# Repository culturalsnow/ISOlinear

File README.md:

ISOlinear is an ortholinear keyboard with the ISO Enter key.

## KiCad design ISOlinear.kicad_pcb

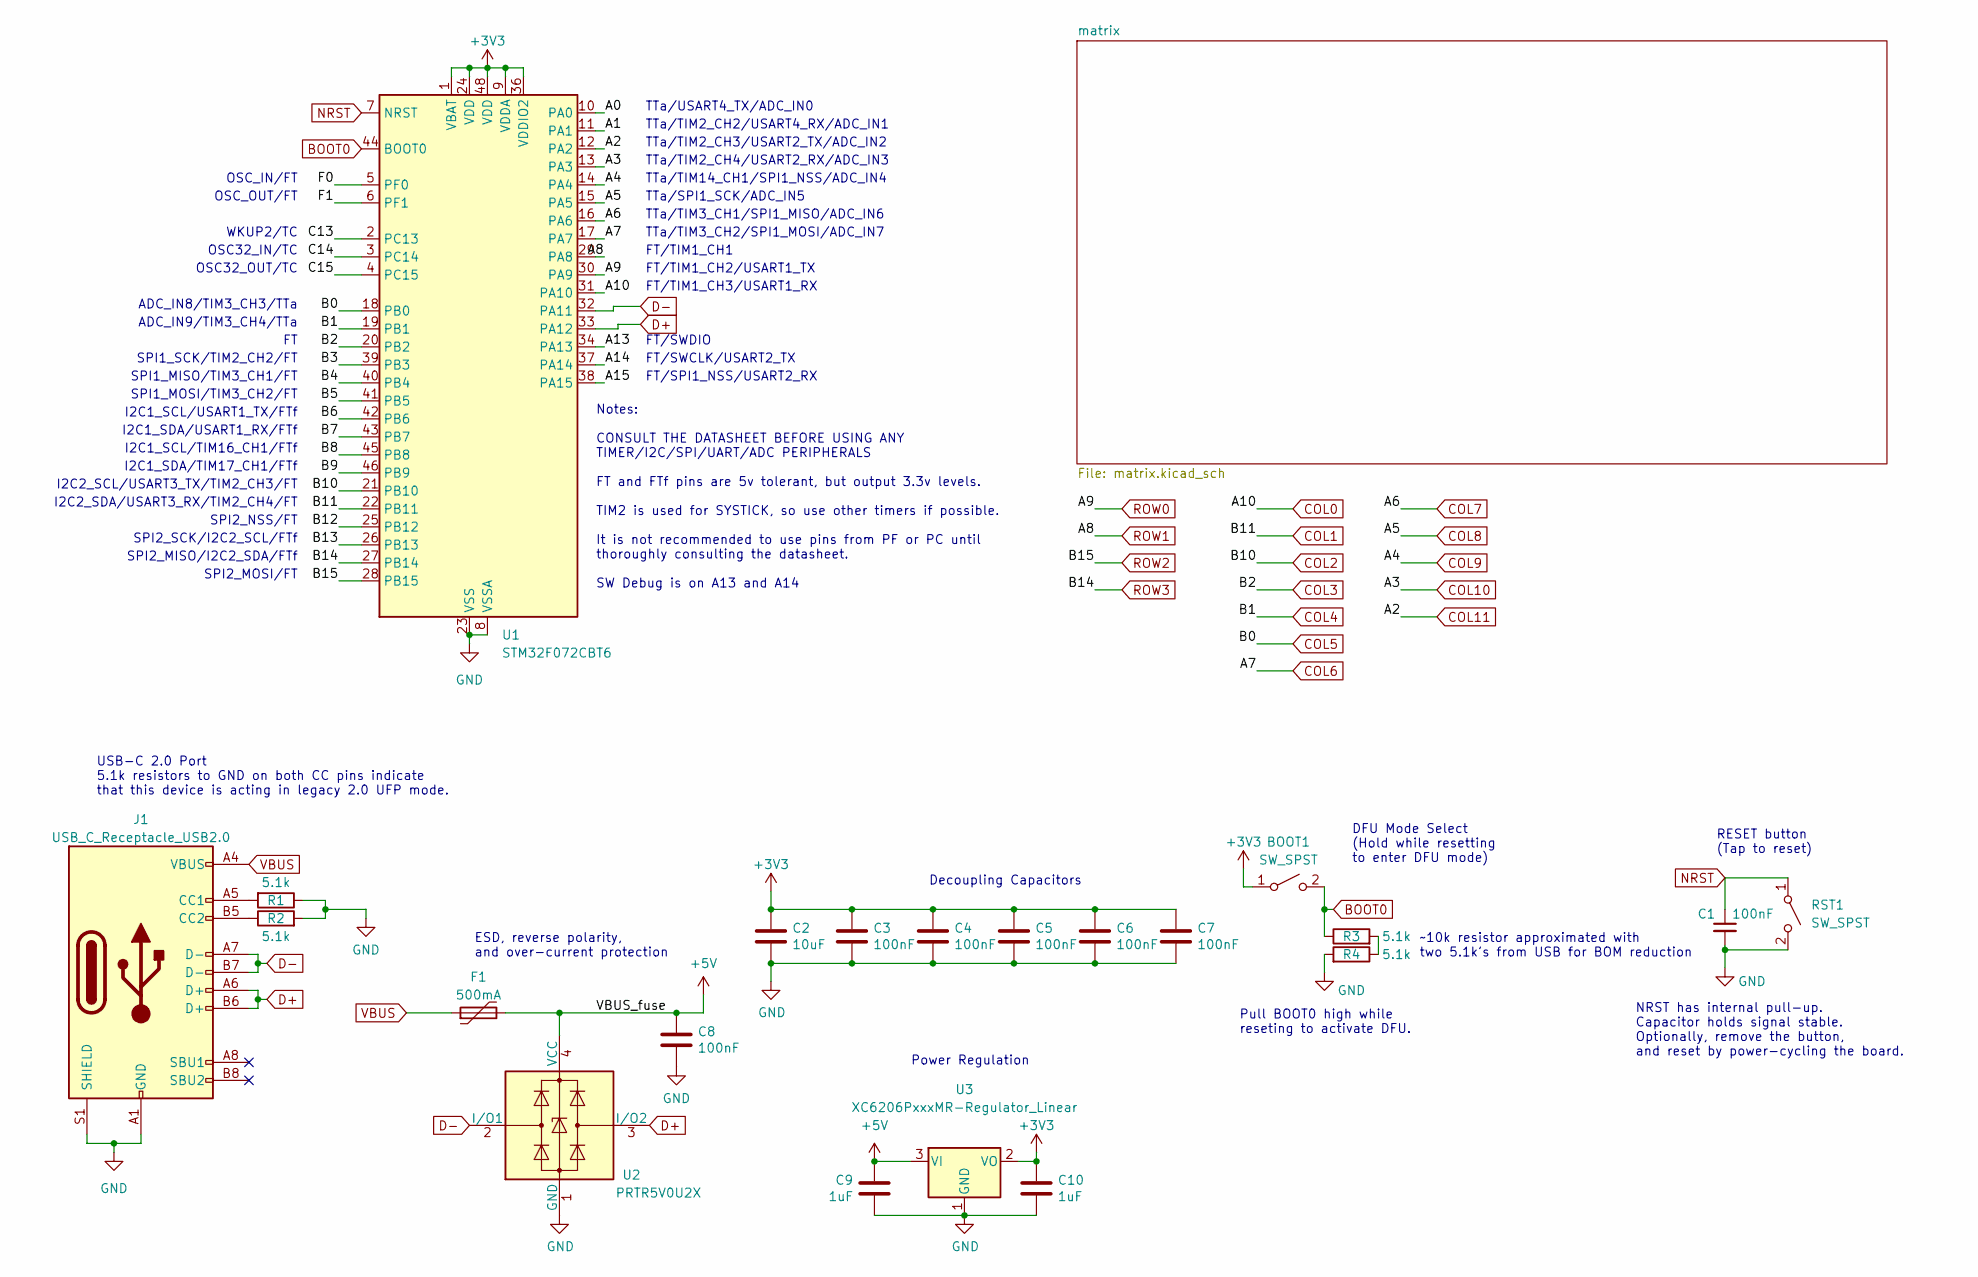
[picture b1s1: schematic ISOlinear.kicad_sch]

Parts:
BOOT1: SW_SPST; SW_SPST_TL3342
C1, C3, C4, C5, C6, C7, C8: 100nF; C_0402_1005Metric; LCSC C307331
C2: 10uF; C_0603_1608Metric; LCSC C307331
C9, C10: 1uF; C_0402_1005Metric; LCSC C307331
F1: 500mA; Fuse_1206_3216Metric; LCSC C135341
J1: USB_C_Receptacle_USB2.0; USB_C_Receptacle_HRO_TYPE-C-31-M-12; JlcRotOffset 180
R1, R2, R3, R4: 5.1k; R_0402_1005Metric
RST1: SW_SPST; SW_SPST_TL3342
U1: STM32F072CBT6; LQFP-48_7x7mm_P0.5mm; JlcRotOffset 90
U2: PRTR5V0U2X; SOT-143; LCSC C2827688
U3: XC6206PxxxMR-Regulator_Linear; SOT-23; LCSC C5446

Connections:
+3V3: BOOT1.1 (A), C2.1, C3.1, C4.1, C5.1, C6.1, C7.1, C10.1, U1.1 (VBAT), U1.9 (VDDA), U1.24 (VDD), U1.36 (VDDIO2), U1.48 (VDD), U3.2 (VO)
+5V: C8.1, C9.1, F1.2, U2.4 (VCC), U3.3 (VI)
/A0: U1.10 (PA0)
/A1: U1.11 (PA1)
/A13: U1.34 (PA13)
/A14: U1.37 (PA14)
/A15: U1.38 (PA15)
/B3: U1.39 (PB3)
/B4: U1.40 (PB4)
/B5: U1.41 (PB5)
/B6: U1.42 (PB6)
/B7: U1.43 (PB7)
/B8: U1.45 (PB8)
/B9: U1.46 (PB9)
/B12: U1.25 (PB12)
/B13: U1.26 (PB13)
/C13: U1.2 (PC13)
/C14: U1.3 (PC14)
/C15: U1.4 (PC15)
/F0: U1.5 (PF0)
/F1: U1.6 (PF1)
BOOT0: BOOT1.2 (B), R3.1, U1.44 (BOOT0)
COL0: U1.31 (PA10); also elsewhere on the board
COL1: U1.22 (PB11); also elsewhere on the board
COL2: U1.21 (PB10); also elsewhere on the board
COL3: U1.20 (PB2); also elsewhere on the board
COL4: U1.19 (PB1); also elsewhere on the board
COL5: U1.18 (PB0); also elsewhere on the board
COL6: U1.17 (PA7); also elsewhere on the board
COL7: U1.16 (PA6); also elsewhere on the board
COL8: U1.15 (PA5); also elsewhere on the board
COL9: U1.14 (PA4); also elsewhere on the board
COL10: U1.13 (PA3); also elsewhere on the board
COL11: U1.12 (PA2); also elsewhere on the board
D+: J1.A6 (D+), J1.B6 (D+), U1.33 (PA12), U2.3 (I/O2)
D-: J1.A7 (D-), J1.B7 (D-), U1.32 (PA11), U2.2 (I/O1)
GND: C1.2, C2.2, C3.2, C4.2, C5.2, C6.2, C7.2, C8.2, C9.2, C10.2, J1.A1 (GND), J1.A12 (GND), J1.B1 (GND), J1.B12 (GND), J1.S1 (SHIELD), R1.1, R2.2, R4.2, RST1.2 (B), U1.8 (VSSA), U1.23 (VSS), U1.35 (VSS), U1.47 (VSS), U2.1 (GND), U3.1 (GND)
NRST: C1.1, RST1.1 (A), U1.7 (NRST)
unnamed: J1.A5 (CC1), R1.2
unnamed: J1.B5 (CC2), R2.1
unnamed: R3.2, R4.1
ROW0: U1.30 (PA9); also elsewhere on the board
ROW1: U1.29 (PA8); also elsewhere on the board
ROW2: U1.28 (PB15); also elsewhere on the board
ROW3: U1.27 (PB14); also elsewhere on the board
VBUS: F1.1, J1.A4 (VBUS), J1.A9 (VBUS), J1.B4 (VBUS), J1.B9 (VBUS)

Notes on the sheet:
SPI1_SCK/TIM2_CH2/FT
FT/TIM1_CH1
FT/TIM1_CH3/USART1_RX
SPI2_NSS/FT
Notes: CONSULT THE DATASHEET BEFORE USING ANY TIMER/I2C/SPI/UART/ADC PERIPHERALS FT and FTf pins are 5v tolerant, but output 3.3v levels. TIM2 is used for SYSTICK, so use other timers if possible. It is not recommended to use pins from PF or PC until thoroughly consulting the datasheet. SW Debug is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
TTa/TIM2_CH4/USART2_RX/ADC_IN3
NRST has internal pull-up. Capacitor holds signal stable. Optionally, remove the button, and reset by power-cycling the board.
FT/SWDIO
Decoupling Capacitors
SPI1_MOSI/TIM3_CH2/FT
ADC_IN9/TIM3_CH4/TTa
I2C2_SCL/USART3_TX/TIM2_CH3/FT
SPI2_MISO/I2C2_SDA/FTf
FT/SWCLK/USART2_TX
I2C1_SCL/TIM16_CH1/FTf
~10k resistor approximated with two 5.1k's from USB for BOM reduction
TTa/TIM2_CH2/USART4_RX/ADC_IN1
USB-C 2.0 Port 5.1k resistors to GND on both CC pins indicate that this device is acting in legacy 2.0 UFP mode.
TTa/TIM2_CH3/USART2_TX/ADC_IN2
OSC_IN/FT
DFU Mode Select (Hold while resetting to enter DFU mode)
WKUP2/TC
I2C2_SDA/USART3_RX/TIM2_CH4/FT
ADC_IN8/TIM3_CH3/TTa
RESET button (Tap to reset)
Pull BOOT0 high while reseting to activate DFU.
I2C1_SDA/TIM17_CH1/FTf
TTa/SPI1_SCK/ADC_IN5
TTa/TIM3_CH1/SPI1_MISO/ADC_IN6
TTa/TIM3_CH2/SPI1_MOSI/ADC_IN7
OSC32_OUT/TC
FT/SPI1_NSS/USART2_RX
SPI1_MISO/TIM3_CH1/FT
OSC32_IN/TC
TTa/TIM14_CH1/SPI1_NSS/ADC_IN4
I2C1_SDA/USART1_RX/FTf
SPI2_MOSI/FT
FT/TIM1_CH2/USART1_TX
Power Regulation
SPI2_SCK/I2C2_SCL/FTf

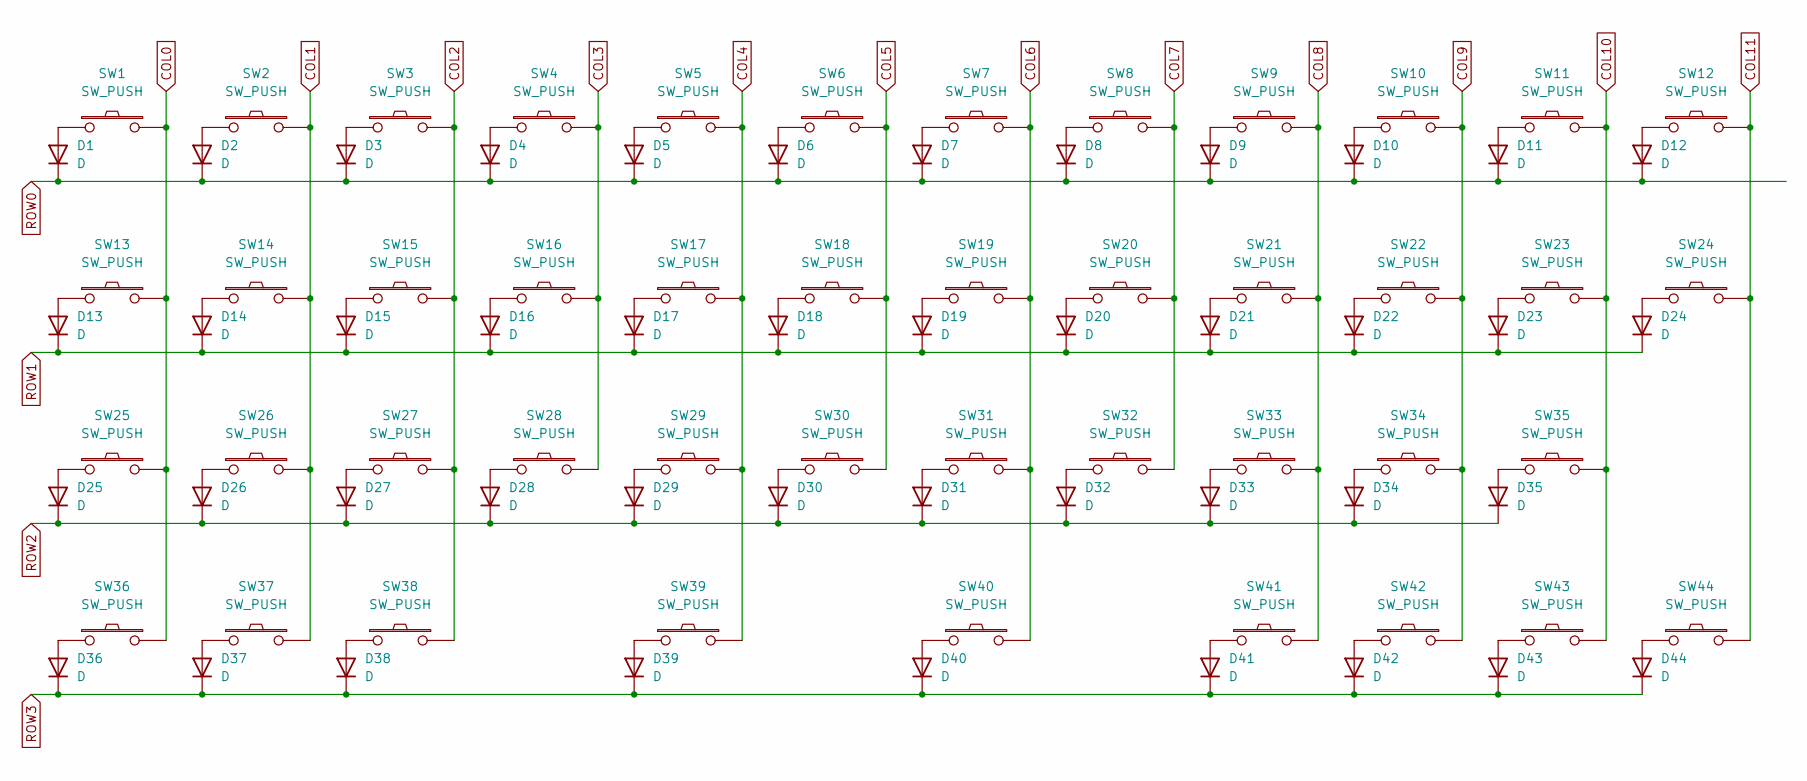
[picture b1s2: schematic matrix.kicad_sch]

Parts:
D1, D2, D3, D4, D5, D6, D7, D8, D9, D10, D11, D12, D13, D14, D15, D16, D17, D18, D19, D20, D21, D22, D23, D24, D25, D26, D27, D28, D29, D30, D31, D32, D33, D34, D35, D36, D37, D38, D39, D40, D41, D42, D43, D44: D; D_SOD-123
SW1, SW2, SW3, SW4, SW5, SW6, SW7, SW8, SW9, SW10, SW11, SW12, SW13, SW14, SW15, SW16, SW17, SW18, SW19, SW20, SW21, SW22, SW23, SW24, SW25, SW26, SW27, SW28, SW29, SW30, SW31, SW32, SW33, SW34, SW35, SW36, SW37, SW38, SW39, SW40, SW41, SW42, SW43, SW44: SW_PUSH; MXOnly-1U-Hotswap

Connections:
COL0: SW1.2, SW13.2, SW25.2, SW36.2; also elsewhere on the board
COL1: SW2.2, SW14.2, SW26.2, SW37.2; also elsewhere on the board
COL2: SW3.2, SW15.2, SW27.2, SW38.2; also elsewhere on the board
COL3: SW4.2, SW16.2, SW28.2; also elsewhere on the board
COL4: SW5.2, SW17.2, SW29.2, SW39.2; also elsewhere on the board
COL5: SW6.2, SW18.2, SW30.2; also elsewhere on the board
COL6: SW7.2, SW19.2, SW31.2, SW40.2; also elsewhere on the board
COL7: SW8.2, SW20.2, SW32.2; also elsewhere on the board
COL8: SW9.2, SW21.2, SW33.2, SW41.2; also elsewhere on the board
COL9: SW10.2, SW22.2, SW34.2, SW42.2; also elsewhere on the board
COL10: SW11.2, SW23.2, SW35.2, SW43.2; also elsewhere on the board
COL11: SW12.2, SW24.2, SW44.2; also elsewhere on the board
unnamed: D1.2 (A), SW1.1
unnamed: D2.2 (A), SW2.1
unnamed: D3.2 (A), SW3.1
unnamed: D4.2 (A), SW4.1
unnamed: D5.2 (A), SW5.1
unnamed: D6.2 (A), SW6.1
unnamed: D7.2 (A), SW7.1
unnamed: D8.2 (A), SW8.1
unnamed: D9.2 (A), SW9.1
unnamed: D10.2 (A), SW10.1
unnamed: D11.2 (A), SW11.1
unnamed: D12.2 (A), SW12.1
unnamed: D13.2 (A), SW13.1
unnamed: D14.2 (A), SW14.1
unnamed: D15.2 (A), SW15.1
unnamed: D16.2 (A), SW16.1
unnamed: D17.2 (A), SW17.1
unnamed: D18.2 (A), SW18.1
unnamed: D19.2 (A), SW19.1
unnamed: D20.2 (A), SW20.1
unnamed: D21.2 (A), SW21.1
unnamed: D22.2 (A), SW22.1
unnamed: D23.2 (A), SW23.1
unnamed: D24.2 (A), SW24.1
unnamed: D25.2 (A), SW25.1
unnamed: D26.2 (A), SW26.1
unnamed: D27.2 (A), SW27.1
unnamed: D28.2 (A), SW28.1
unnamed: D29.2 (A), SW29.1
unnamed: D30.2 (A), SW30.1
unnamed: D31.2 (A), SW31.1
unnamed: D32.2 (A), SW32.1
unnamed: D33.2 (A), SW33.1
unnamed: D34.2 (A), SW34.1
unnamed: D35.2 (A), SW35.1
unnamed: D36.2 (A), SW36.1
unnamed: D37.2 (A), SW37.1
unnamed: D38.2 (A), SW38.1
unnamed: D39.2 (A), SW39.1
unnamed: D40.2 (A), SW40.1
unnamed: D41.2 (A), SW41.1
unnamed: D42.2 (A), SW42.1
unnamed: D43.2 (A), SW43.1
unnamed: D44.2 (A), SW44.1
ROW0: D1.1 (K), D2.1 (K), D3.1 (K), D4.1 (K), D5.1 (K), D6.1 (K), D7.1 (K), D8.1 (K), D9.1 (K), D10.1 (K), D11.1 (K), D12.1 (K); also elsewhere on the board
ROW1: D13.1 (K), D14.1 (K), D15.1 (K), D16.1 (K), D17.1 (K), D18.1 (K), D19.1 (K), D20.1 (K), D21.1 (K), D22.1 (K), D23.1 (K), D24.1 (K); also elsewhere on the board
ROW2: D25.1 (K), D26.1 (K), D27.1 (K), D28.1 (K), D29.1 (K), D30.1 (K), D31.1 (K), D32.1 (K), D33.1 (K), D34.1 (K), D35.1 (K); also elsewhere on the board
ROW3: D36.1 (K), D37.1 (K), D38.1 (K), D39.1 (K), D40.1 (K), D41.1 (K), D42.1 (K), D43.1 (K), D44.1 (K); also elsewhere on the board

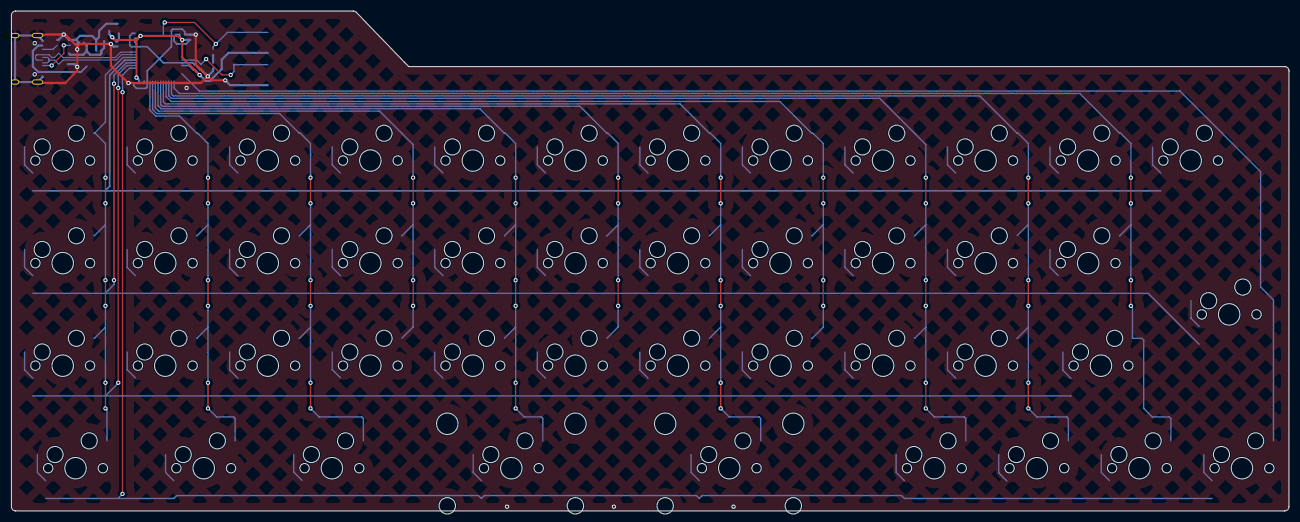
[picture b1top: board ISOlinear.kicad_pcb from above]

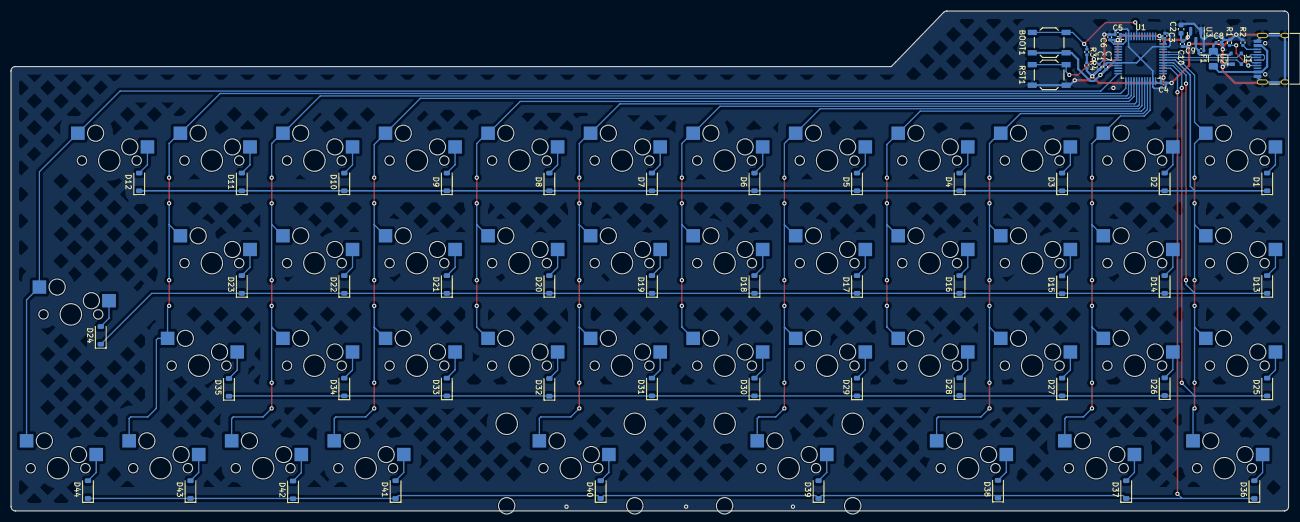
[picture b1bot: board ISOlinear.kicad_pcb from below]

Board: 2 copper layers, 237.3 x 92.9 mm, 109 parts (65 on the bottom side), 71 nets.

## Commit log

2026-01-20 1/20
    Initial push
2026-01-20 Update README.md
    README.md updated
2026-01-20 1/21
    Initial schematic/pcb setup, no routing and no global labels connected
2026-01-21 1/21
    Reset grid origin, placed stab footprints
2026-01-21 1/21
    changed layout to teeth version, started routing rows and columns
2026-01-21 1/21
    Matrix routing done
2026-01-21 1/22
    Routing solutions brainstorm
2026-01-22 1/23
    routed and filled tentatively, no grounds on some pins
2026-01-24 1/24
    updated zones, need to fix footprint and edge cuts around usb
